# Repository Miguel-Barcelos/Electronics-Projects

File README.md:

# Controle motor elétrico PMSM
Este repositório contém projetos de eletrônica, incluindo circuitos eletrônicos, simulações e design de PCBs.

## Visão Geral do Projeto
O objetivo principal deste trabalho é 

## 📂 Estrutura do Repositório

*   `/data`: xxxxxxxxxxxxxxxxxxxxxxxxxxxxxxxxxxxxxxxxxxxxxxxxxxxxxxxxx
*   `/src`: xxxxxxxxxxxxxxxxxxxxxxxxxxxxxxxxxxxxxxxxxxxxxxxxxxxxxxxxx
*   `/project`: xxxxxxxxxxxxxxxxxxxxxxxxxxxxxxxxxxxxxxxxxxxxxxxxxxxxxxxxx
*   `/figures`: xxxxxxxxxxxxxxxxxxxxxxxxxxxxxxxxxxxxxxxxxxxxxxxxxxxxxxxxx

## 🎛️ Detalhes do Sistema Dinâmico

xxxxxxxxxxxxxxxxxxxxxxxxxxxxxxxxxxxxxxxxxxxxxxxxxxxxxxxxx

## 💻 Requisitos e Tecnologias

xxxxxxxxxxxxxxxxxxxxxxxxxxxxxxxxxxxxxxxxxxxxxxxxxxxxxxxxx

### Toolboxes Necessárias:
* xxxxxxxxxxxxxxxxxxxxxxxxxxxxxxxxxxxxxxxxxxxxxxxxxxxxxxxxx
* xxxxxxxxxxxxxxxxxxxxxxxxxxxxxxxxxxxxxxxxxxxxxxxxxxxxxxxxx

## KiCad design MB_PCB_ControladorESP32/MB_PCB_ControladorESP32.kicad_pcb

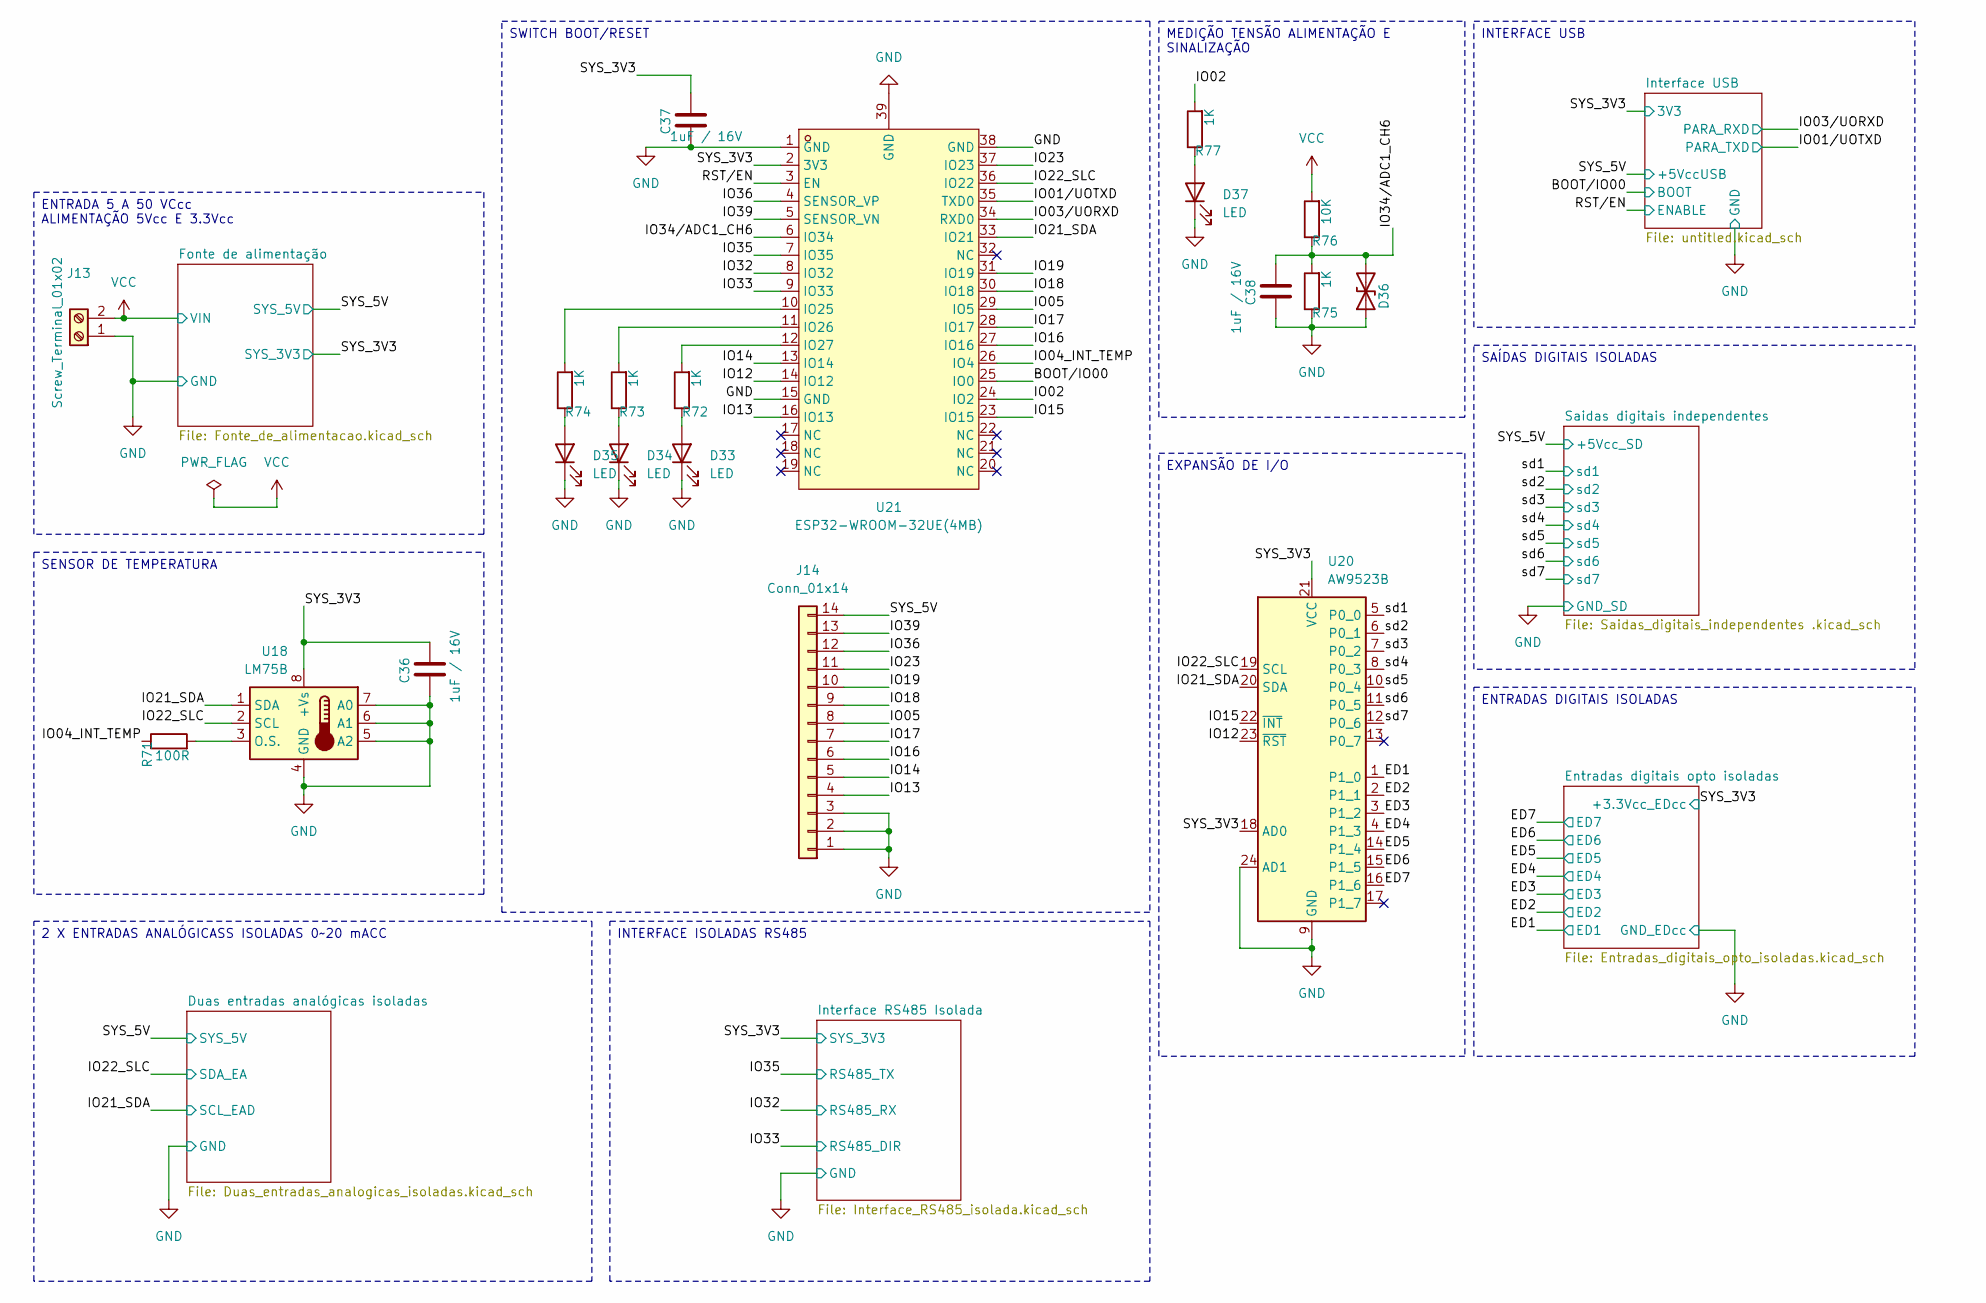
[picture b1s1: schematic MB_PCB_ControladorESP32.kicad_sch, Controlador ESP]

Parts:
C36, C37, C38: 1uF / 16V; C_Elec_4x5.4
D33, D34, D35, D37: LED; LED_0805_2012Metric_Pad1.15x1.40mm_HandSolder
D36: D_TVS; SOD-523_L1.2-W0.8-LS1.6-BI
J13: Screw_Terminal_01x02; TerminalBlock_TE_282834-2_1x02_P2.54mm_Horizontal
J14: Conn_01x14; PinHeader_1x14_P2.54mm_Vertical
R71: 100R; R_0805_2012Metric_Pad1.20x1.40mm_HandSolder
R72, R73, R74, R75, R77: 1K; R_0805_2012Metric_Pad1.20x1.40mm_HandSolder
R76: 10K; R_0805_2012Metric_Pad1.20x1.40mm_HandSolder
U18: LM75B; SOP-8_3.76x4.96mm_P1.27mm
U20: AW9523B; QFN-24-1EP_4x4mm_P0.5mm_EP2.7x2.7mm
U21: ESP32-WROOM-32UE(4MB); WIFI-SMD_ESP32-WROOM-32UE; LCSC Part C701344

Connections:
+3.3Vcc_EDcc: C36.2, C37.2, U18.8 (+Vs), U20.18 (AD0), U20.21 (VCC), U21.2 (3V3); also elsewhere on the board
+5VccUSB: J14.14; also elsewhere on the board
/BOOT/IO00: U21.25 (IO0); also elsewhere on the board
/ED1: U20.1 (P1_0); also elsewhere on the board
/ED2: U20.2 (P1_1); also elsewhere on the board
/ED3: U20.3 (P1_2); also elsewhere on the board
/ED4: U20.4 (P1_3); also elsewhere on the board
/ED5: U20.14 (P1_4); also elsewhere on the board
/ED6: U20.15 (P1_5); also elsewhere on the board
/ED7: U20.16 (P1_6); also elsewhere on the board
/IO01/UOTXD: U21.35 (TXD0); also elsewhere on the board
/IO02: R77.2, U21.24 (IO2)
/IO03/UORXD: U21.34 (RXD0); also elsewhere on the board
/IO04_INT_TEMP: R71.1, U21.26 (IO4)
/IO05: J14.8, U21.29 (IO5)
/IO12: U20.23 (~RST), U21.14 (IO12)
/IO13: J14.4, U21.16 (IO13)
/IO14: J14.5, U21.13 (IO14)
/IO15: U20.22 (~INT), U21.23 (IO15)
/IO16: J14.6, U21.27 (IO16)
/IO17: J14.7, U21.28 (IO17)
/IO18: J14.9, U21.30 (IO18)
/IO19: J14.10, U21.31 (IO19)
/IO21_SDA: U18.1 (SDA), U20.20 (SDA), U21.33 (IO21); also elsewhere on the board
/IO22_SLC: U18.2 (SCL), U20.19 (SCL), U21.36 (IO22); also elsewhere on the board
/IO23: J14.11, U21.37 (IO23)
/IO32: U21.8 (IO32); also elsewhere on the board
/IO33: U21.9 (IO33); also elsewhere on the board
/IO34/ADC1_CH6: C38.2, D36.2 (A2), R75.2, R76.1, U21.6 (IO34)
/IO35: U21.7 (IO35); also elsewhere on the board
/IO36: J14.12, U21.4 (SENSOR_VP)
/IO39: J14.13, U21.5 (SENSOR_VN)
/RST/EN: U21.3 (EN); also elsewhere on the board
/sd1: U20.5 (P0_0); also elsewhere on the board
/sd2: U20.6 (P0_1); also elsewhere on the board
/sd3: U20.7 (P0_2); also elsewhere on the board
/sd4: U20.8 (P0_3); also elsewhere on the board
/sd5: U20.10 (P0_4); also elsewhere on the board
/sd6: U20.11 (P0_5); also elsewhere on the board
/sd7: U20.12 (P0_6); also elsewhere on the board
GND: C36.1, C37.1, C38.1, D33.1 (K), D34.1 (K), D35.1 (K), D36.1 (A1), D37.1 (K), J13.1, J14.1, J14.2, J14.3, R75.1, U18.4 (GND), U18.5 (A2), U18.6 (A1), U18.7 (A0), U20.9 (GND), U20.24 (AD1), U20.25 (GND), U21.1 (GND), U21.15 (GND), U21.38 (GND), U21.39 (GND); also elsewhere on the board
unnamed: D33.2 (A), R72.1
unnamed: D34.2 (A), R73.1
unnamed: D35.2 (A), R74.1
unnamed: D37.2 (A), R77.1
unnamed: R71.2, U18.3 (O.S.)
unnamed: R74.2, U21.10 (IO25)
unnamed: R73.2, U21.11 (IO26)
unnamed: R72.2, U21.12 (IO27)
VCC: J13.2, R76.2; also elsewhere on the board

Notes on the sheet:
INTERFACE ISOLADAS RS485
2 X ENTRADAS ANALÓGICASS ISOLADAS 0~20 mACC
SWITCH BOOT/RESET
SAÍDAS DIGITAIS ISOLADAS
ENTRADAS DIGITAIS ISOLADAS
EXPANSÃO DE I/O
ENTRADA 5 A 50 VCcc ALIMENTAÇÃO 5Vcc E 3.3Vcc
SENSOR DE TEMPERATURA
MEDIÇÃO TENSÃO ALIMENTAÇÃO E SINALIZAÇÃO
INTERFACE USB

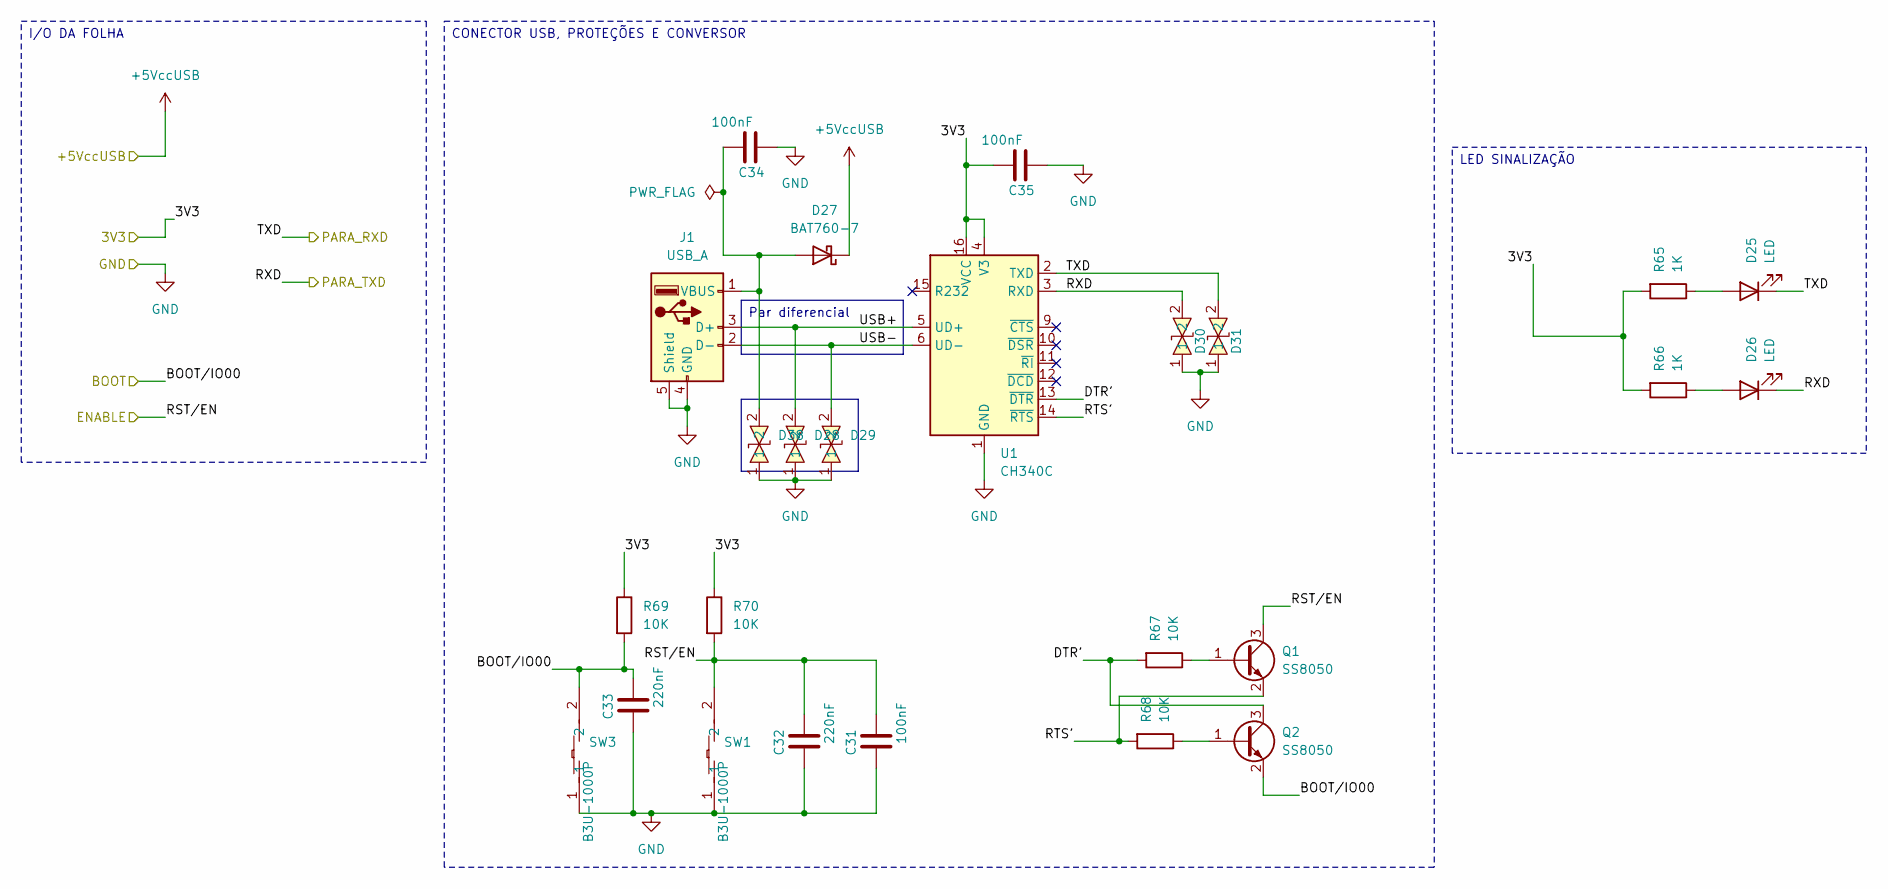
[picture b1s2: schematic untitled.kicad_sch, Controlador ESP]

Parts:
C31, C34, C35: 100nF; C_Elec_8x5.4
C32, C33: 220nF; C_Elec_8x5.4
D25, D26: LED; LED_0805_2012Metric_Pad1.15x1.40mm_HandSolder
D27: BAT760-7; SOD-523_L1.2-W0.8-LS1.6-BI
D28, D29, D30, D31, D38: LESD5D5.0CT1G; SOD-523_L1.2-W0.8-LS1.6-BI; LCSC Part C383211
J1: USB_A; USB_A_Molex_67643_Horizontal
Q1, Q2: SS8050; SOT-23
R65, R66: 1K; R_0805_2012Metric_Pad1.20x1.40mm_HandSolder
R67, R68, R69, R70: 10K; R_0805_2012Metric_Pad1.20x1.40mm_HandSolder
SW1, SW3: B3U-1000P; KEY-SMD_B3U-1000PM; LCSC Part C231329
U1: CH340C; SOIC-16_3.9x9.9mm_P1.27mm

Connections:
+3.3Vcc_EDcc: C35.2, R65.2, R66.2, R69.1, R70.1, U1.4 (V3), U1.16 (VCC); also elsewhere on the board
+5VccUSB: D27.1 (K); also elsewhere on the board
/BOOT/IO00: C33.2, Q2.2 (E), R69.2, SW3.2; also elsewhere on the board
/IO01/UOTXD: D26.1 (K), D30.2, U1.3 (RXD); also elsewhere on the board
/IO03/UORXD: D25.1 (K), D31.2, U1.2 (TXD); also elsewhere on the board
/Interface USB/DTR': Q2.3 (C), R67.2, U1.13 (~DTR)
/Interface USB/RTS': Q1.2 (E), R68.2, U1.14 (~RTS)
/Interface USB/USB+: D28.2, J1.3 (D+), U1.5 (UD+)
/Interface USB/USB-: D29.2, J1.2 (D-), U1.6 (UD-)
/RST/EN: C31.2, C32.2, Q1.3 (C), R70.2, SW1.2; also elsewhere on the board
GND: C31.1, C32.1, C33.1, C34.1, C35.1, D28.1, D29.1, D30.1, D31.1, D38.1, J1.4 (GND), J1.5 (Shield), SW1.1, SW3.1, U1.1 (GND); also elsewhere on the board
unnamed: D25.2 (A), R65.1
unnamed: D26.2 (A), R66.1
unnamed: C34.2, D27.2 (A), D38.2, J1.1 (VBUS)
unnamed: Q1.1 (B), R67.1
unnamed: Q2.1 (B), R68.1

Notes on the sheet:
I/O DA FOLHA
LED SINALIZAÇÃO
CONECTOR USB, PROTEÇÕES E CONVERSOR
Par diferencial

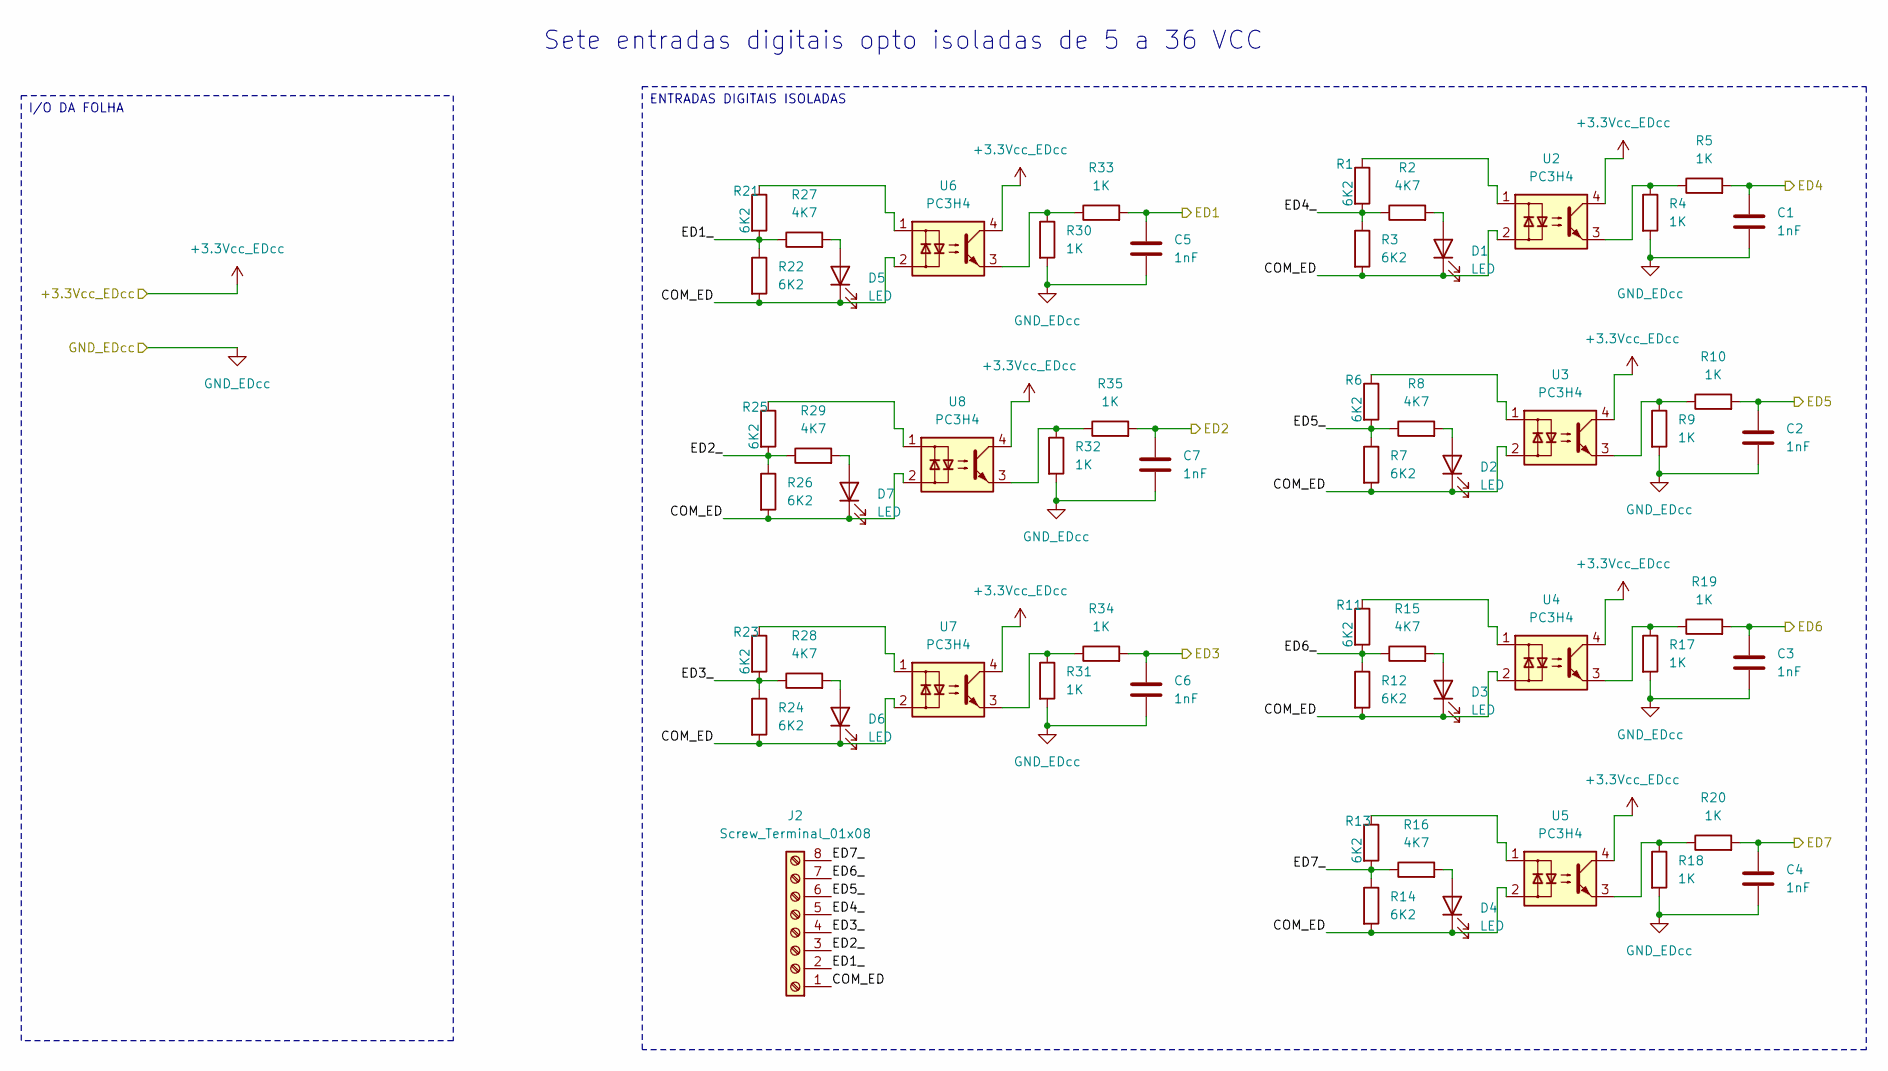
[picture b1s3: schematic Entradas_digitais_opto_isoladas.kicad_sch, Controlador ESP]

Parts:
C1, C2, C3, C4, C5, C6, C7: 1nF; C_1206_3216Metric_Pad1.33x1.80mm_HandSolder
D1, D2, D3, D4, D5, D6, D7: LED; LED_0805_2012Metric_Pad1.15x1.40mm_HandSolder
J2: Screw_Terminal_01x08; TerminalBlock_TE_282834-8_1x08_P2.54mm_Horizontal
R1, R3, R6, R7, R11, R12, R13, R14, R21, R22, R23, R24, R25, R26: 6K2; R_0805_2012Metric_Pad1.20x1.40mm_HandSolder
R2, R8, R15, R16, R27, R28, R29: 4K7; R_0805_2012Metric_Pad1.20x1.40mm_HandSolder
R4, R5, R9, R10, R17, R18, R19, R20, R30, R31, R32, R33, R34, R35: 1K; R_0805_2012Metric_Pad1.20x1.40mm_HandSolder
U2, U3, U4, U5, U6, U7, U8: PC3H4; SMDIP-4_W7.62mm

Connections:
+3.3Vcc_EDcc: U2.4, U3.4, U4.4, U5.4, U6.4, U7.4, U8.4; also elsewhere on the board
/ED1: C5.1, R33.2; also elsewhere on the board
/ED2: C7.1, R35.2; also elsewhere on the board
/ED3: C6.1, R34.2; also elsewhere on the board
/ED4: C1.1, R5.2; also elsewhere on the board
/ED5: C2.1, R10.2; also elsewhere on the board
/ED6: C3.1, R19.2; also elsewhere on the board
/ED7: C4.1, R20.2; also elsewhere on the board
/Entradas digitais opto isoladas/COM_ED: D1.1 (K), D2.1 (K), D3.1 (K), D4.1 (K), D5.1 (K), D6.1 (K), D7.1 (K), J2.1, R3.2, R7.2, R12.2, R14.2, R22.2, R24.2, R26.2, U2.2, U3.2, U4.2, U5.2, U6.2, U7.2, U8.2
/Entradas digitais opto isoladas/ED1_: J2.2, R21.2, R22.1, R27.1
/Entradas digitais opto isoladas/ED2_: J2.3, R25.2, R26.1, R29.1
/Entradas digitais opto isoladas/ED3_: J2.4, R23.2, R24.1, R28.1
/Entradas digitais opto isoladas/ED4_: J2.5, R1.2, R2.1, R3.1
/Entradas digitais opto isoladas/ED5_: J2.6, R6.2, R7.1, R8.1
/Entradas digitais opto isoladas/ED6_: J2.7, R11.2, R12.1, R15.1
/Entradas digitais opto isoladas/ED7_: J2.8, R13.2, R14.1, R16.1
GND: C1.2, C2.2, C3.2, C4.2, C5.2, C6.2, C7.2, R4.2, R9.2, R17.2, R18.2, R30.2, R31.2, R32.2; also elsewhere on the board
unnamed: D1.2 (A), R2.2
unnamed: D2.2 (A), R8.2
unnamed: D3.2 (A), R15.2
unnamed: D4.2 (A), R16.2
unnamed: D5.2 (A), R27.2
unnamed: D6.2 (A), R28.2
unnamed: D7.2 (A), R29.2
unnamed: R1.1, U2.1
unnamed: R4.1, R5.1, U2.3
unnamed: R6.1, U3.1
unnamed: R9.1, R10.1, U3.3
unnamed: R11.1, U4.1
unnamed: R13.1, U5.1
unnamed: R17.1, R19.1, U4.3
unnamed: R18.1, R20.1, U5.3
unnamed: R21.1, U6.1
unnamed: R23.1, U7.1
unnamed: R25.1, U8.1
unnamed: R30.1, R33.1, U6.3
unnamed: R31.1, R34.1, U7.3
unnamed: R32.1, R35.1, U8.3

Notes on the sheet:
Sete entradas digitais opto isoladas de 5 a 36 VCC
I/O DA FOLHA
ENTRADAS DIGITAIS ISOLADAS

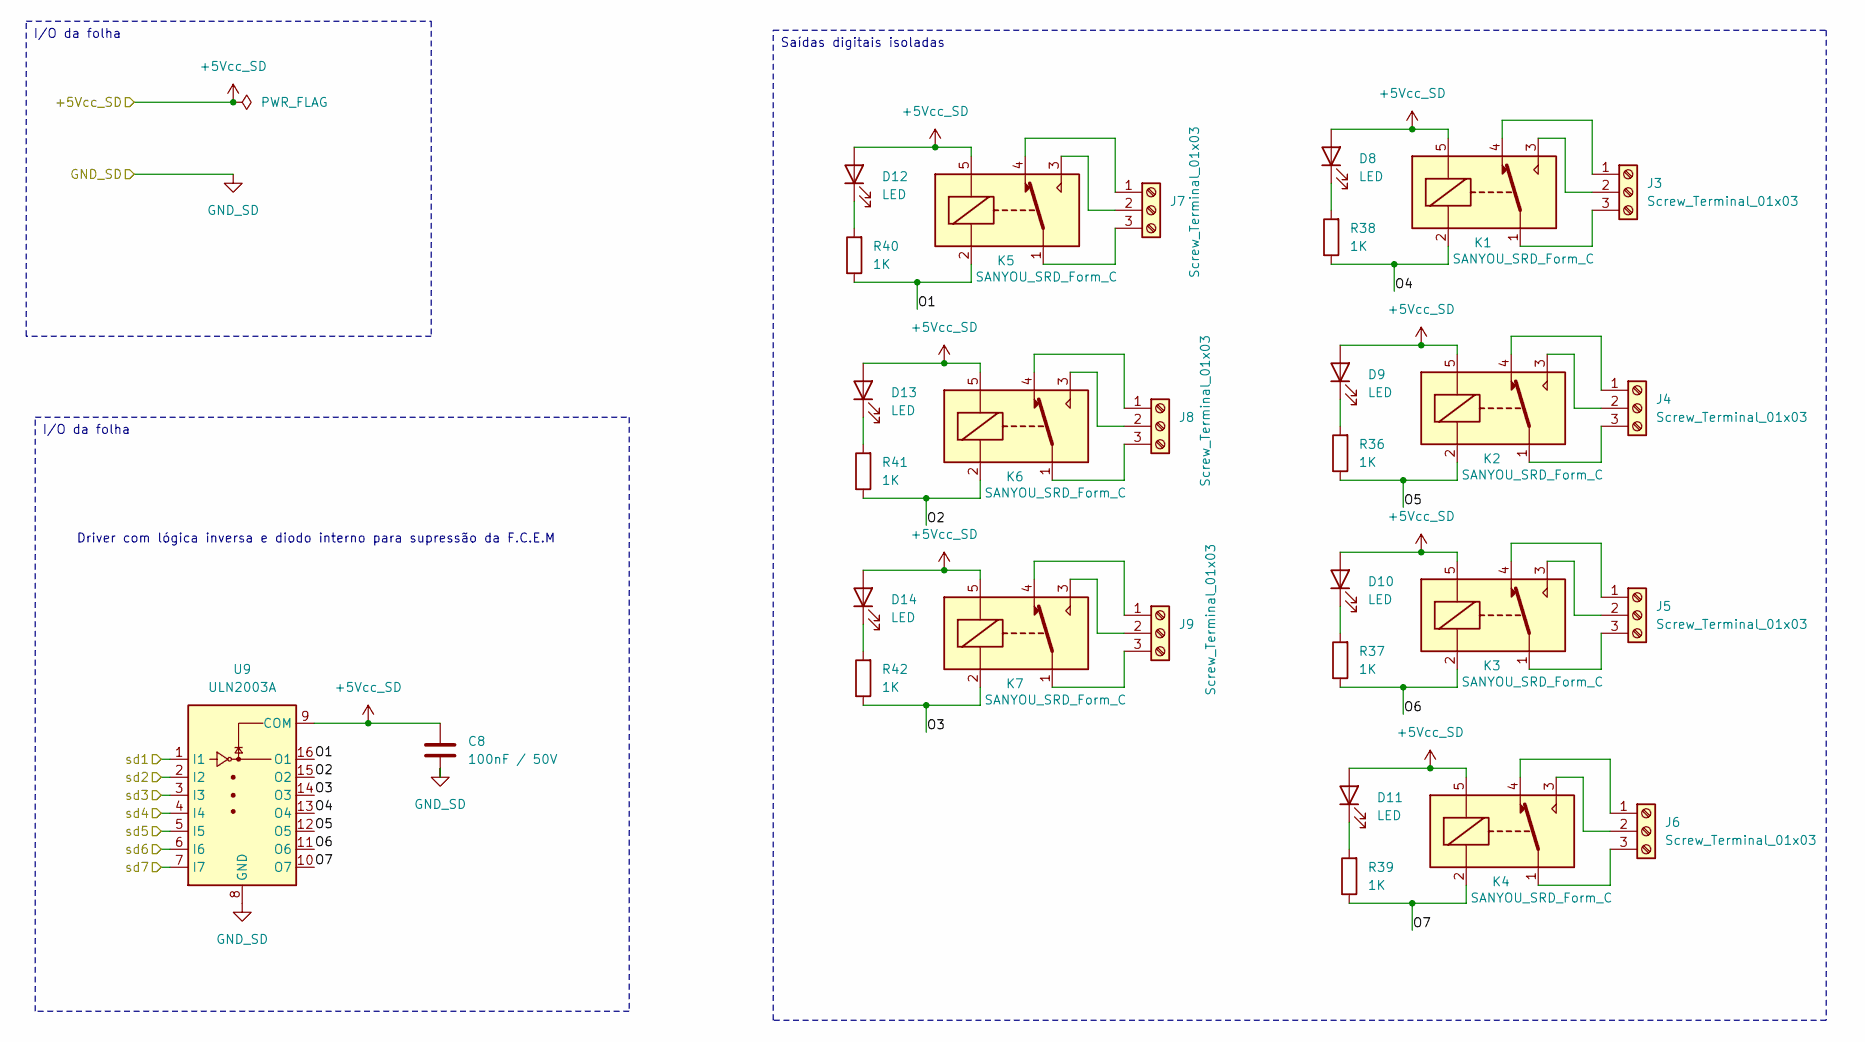
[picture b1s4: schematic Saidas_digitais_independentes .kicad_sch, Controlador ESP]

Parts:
C8: 100nF / 50V; C_1206_3216Metric_Pad1.33x1.80mm_HandSolder
D8, D9, D10, D11, D12, D13, D14: LED; LED_0805_2012Metric_Pad1.15x1.40mm_HandSolder
J3, J4, J5, J6, J7, J8, J9: Screw_Terminal_01x03; TerminalBlock_TE_282834-3_1x03_P2.54mm_Horizontal
K1, K2, K3, K4, K5, K6, K7: SANYOU_SRD_Form_C; Relay_SPDT_SANYOU_SRD_Series_Form_C
R36, R37, R38, R39, R40, R41, R42: 1K; R_0805_2012Metric_Pad1.20x1.40mm_HandSolder
U9: ULN2003A; DIP-16_W7.62mm

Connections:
+5VccUSB: C8.1, D8.2 (A), D9.2 (A), D10.2 (A), D11.2 (A), D12.2 (A), D13.2 (A), D14.2 (A), K1.5, K2.5, K3.5, K4.5, K5.5, K6.5, K7.5, U9.9 (COM); also elsewhere on the board
/Saidas digitais independentes/O1: K5.2, R40.1, U9.16 (O1)
/Saidas digitais independentes/O2: K6.2, R41.1, U9.15 (O2)
/Saidas digitais independentes/O3: K7.2, R42.1, U9.14 (O3)
/Saidas digitais independentes/O4: K1.2, R38.1, U9.13 (O4)
/Saidas digitais independentes/O5: K2.2, R36.1, U9.12 (O5)
/Saidas digitais independentes/O6: K3.2, R37.1, U9.11 (O6)
/Saidas digitais independentes/O7: K4.2, R39.1, U9.10 (O7)
/sd1: U9.1 (I1); also elsewhere on the board
/sd2: U9.2 (I2); also elsewhere on the board
/sd3: U9.3 (I3); also elsewhere on the board
/sd4: U9.4 (I4); also elsewhere on the board
/sd5: U9.5 (I5); also elsewhere on the board
/sd6: U9.6 (I6); also elsewhere on the board
/sd7: U9.7 (I7); also elsewhere on the board
GND: C8.2, U9.8 (GND); also elsewhere on the board
unnamed: D8.1 (K), R38.2
unnamed: D9.1 (K), R36.2
unnamed: D10.1 (K), R37.2
unnamed: D11.1 (K), R39.2
unnamed: D12.1 (K), R40.2
unnamed: D13.1 (K), R41.2
unnamed: D14.1 (K), R42.2
unnamed: J3.1, K1.4
unnamed: J3.2, K1.3
unnamed: J3.3, K1.1
unnamed: J4.1, K2.4
unnamed: J4.2, K2.3
unnamed: J4.3, K2.1
unnamed: J5.1, K3.4
unnamed: J5.2, K3.3
unnamed: J5.3, K3.1
unnamed: J6.1, K4.4
unnamed: J6.2, K4.3
unnamed: J6.3, K4.1
unnamed: J7.1, K5.4
unnamed: J7.2, K5.3
unnamed: J7.3, K5.1
unnamed: J8.1, K6.4
unnamed: J8.2, K6.3
unnamed: J8.3, K6.1
unnamed: J9.1, K7.4
unnamed: J9.2, K7.3
unnamed: J9.3, K7.1

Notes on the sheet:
Driver com lógica inversa e diodo interno para supressão da F.C.E.M
Saídas digitais isoladas
I/O da folha
I/O da folha

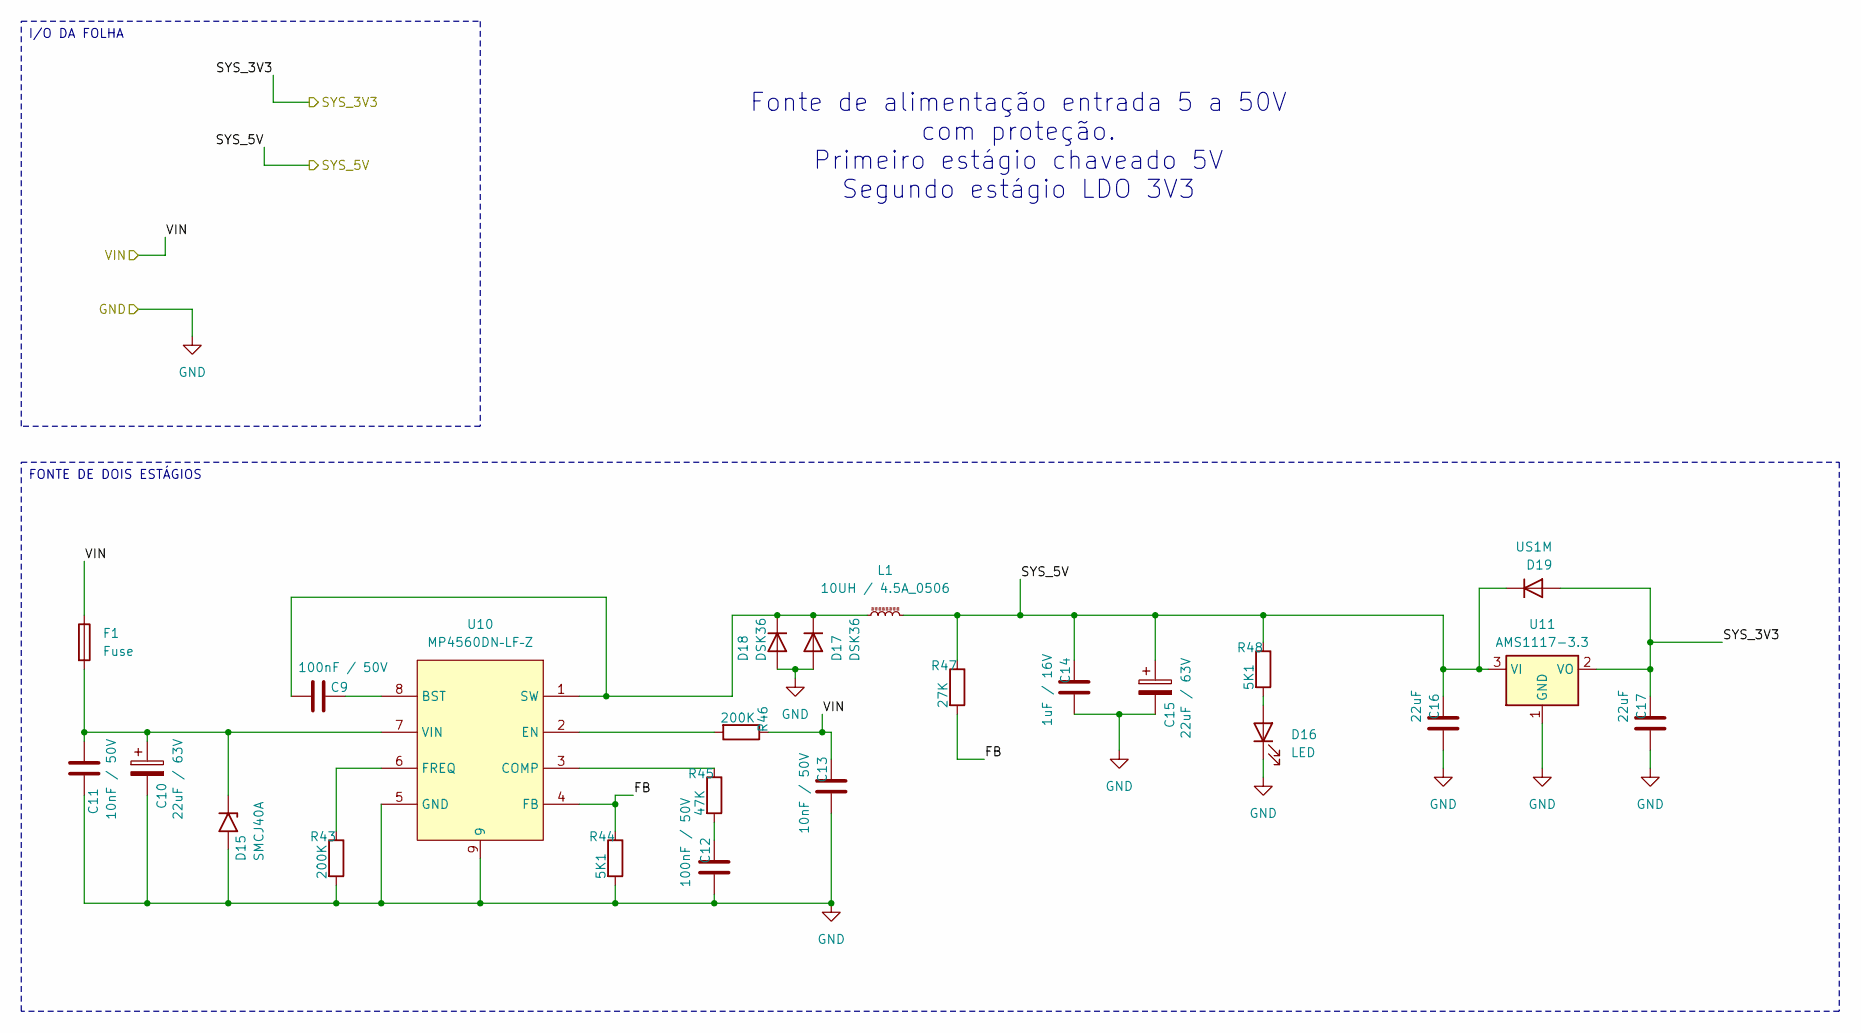
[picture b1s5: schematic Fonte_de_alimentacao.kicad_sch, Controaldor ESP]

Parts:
C9, C12: 100nF / 50V; C_0805_2012Metric_Pad1.18x1.45mm_HandSolder
C10: 22uF / 63V; CP_Elec_6.3x5.9
C11: 10nF / 50V; C_0805_2012Metric_Pad1.18x1.45mm_HandSolder
C13: 10nF / 50V; CP_Elec_10x12.5
C14: 1uF / 16V; C_Elec_3x5.4
C15: 22uF / 63V; CP_Elec_10x12.5
C16, C17: 22uF; C_Elec_8x5.4
D15: SMCJ40A; D_SMC
D16: LED; LED_0805_2012Metric_Pad1.15x1.40mm_HandSolder
D17, D18: DSK36; D_SOD-523
D19: US1M; D_SMA
F1: Fuse; Fuse_Bourns_MF-RG300
L1: 10UH / 4.5A_0506; L_Cenker_CKCS6020
R43, R46: 200K; R_0805_2012Metric_Pad1.20x1.40mm_HandSolder
R44, R48: 5K1; R_0805_2012Metric_Pad1.20x1.40mm_HandSolder
R45: 47K; R_0805_2012Metric_Pad1.20x1.40mm_HandSolder
R47: 27K; R_0805_2012Metric_Pad1.20x1.40mm_HandSolder
U10: MP4560DN–LF–Z; SOIC-8_L4.9-W3.9-P1.27-LS6.0-BL-EP3.1-1; LCSC Part C40133
U11: AMS1117-3.3; SOT-223-3_TabPin2

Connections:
+3.3Vcc_EDcc: C17.2, D19.2 (A), U11.2 (VO); also elsewhere on the board
+5VccUSB: C14.2, C15.1, C16.2, D19.1 (K), L1.2, R47.1, R48.1, U11.3 (VI); also elsewhere on the board
/Fonte de alimentação/FB: R44.1, R47.2, U10.4 (FB)
GND: C10.2, C11.1, C12.1, C13.1, C14.1, C15.2, C16.1, C17.1, D15.2 (A2), D16.1 (K), D17.2 (A), D18.2 (A), R43.2, R44.2, U10.5 (GND), U10.9, U11.1 (GND); also elsewhere on the board
unnamed: C12.2, R45.2
unnamed: C10.1, C11.2, D15.1 (A1), F1.2, U10.7 (VIN)
unnamed: D16.2 (A), R48.2
unnamed: C9.1, D17.1 (K), D18.1 (K), L1.1, U10.1 (SW)
unnamed: C9.2, U10.8 (BST)
unnamed: R45.1, U10.3 (COMP)
unnamed: R46.2, U10.2 (EN)
unnamed: R43.1, U10.6 (FREQ)
VCC: C13.2, F1.1, R46.1; also elsewhere on the board

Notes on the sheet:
Fonte de alimentação entrada 5 a 50V com proteção. Primeiro estágio chaveado 5V Segundo estágio LDO 3V3
FONTE DE DOIS ESTÁGIOS
I/O DA FOLHA

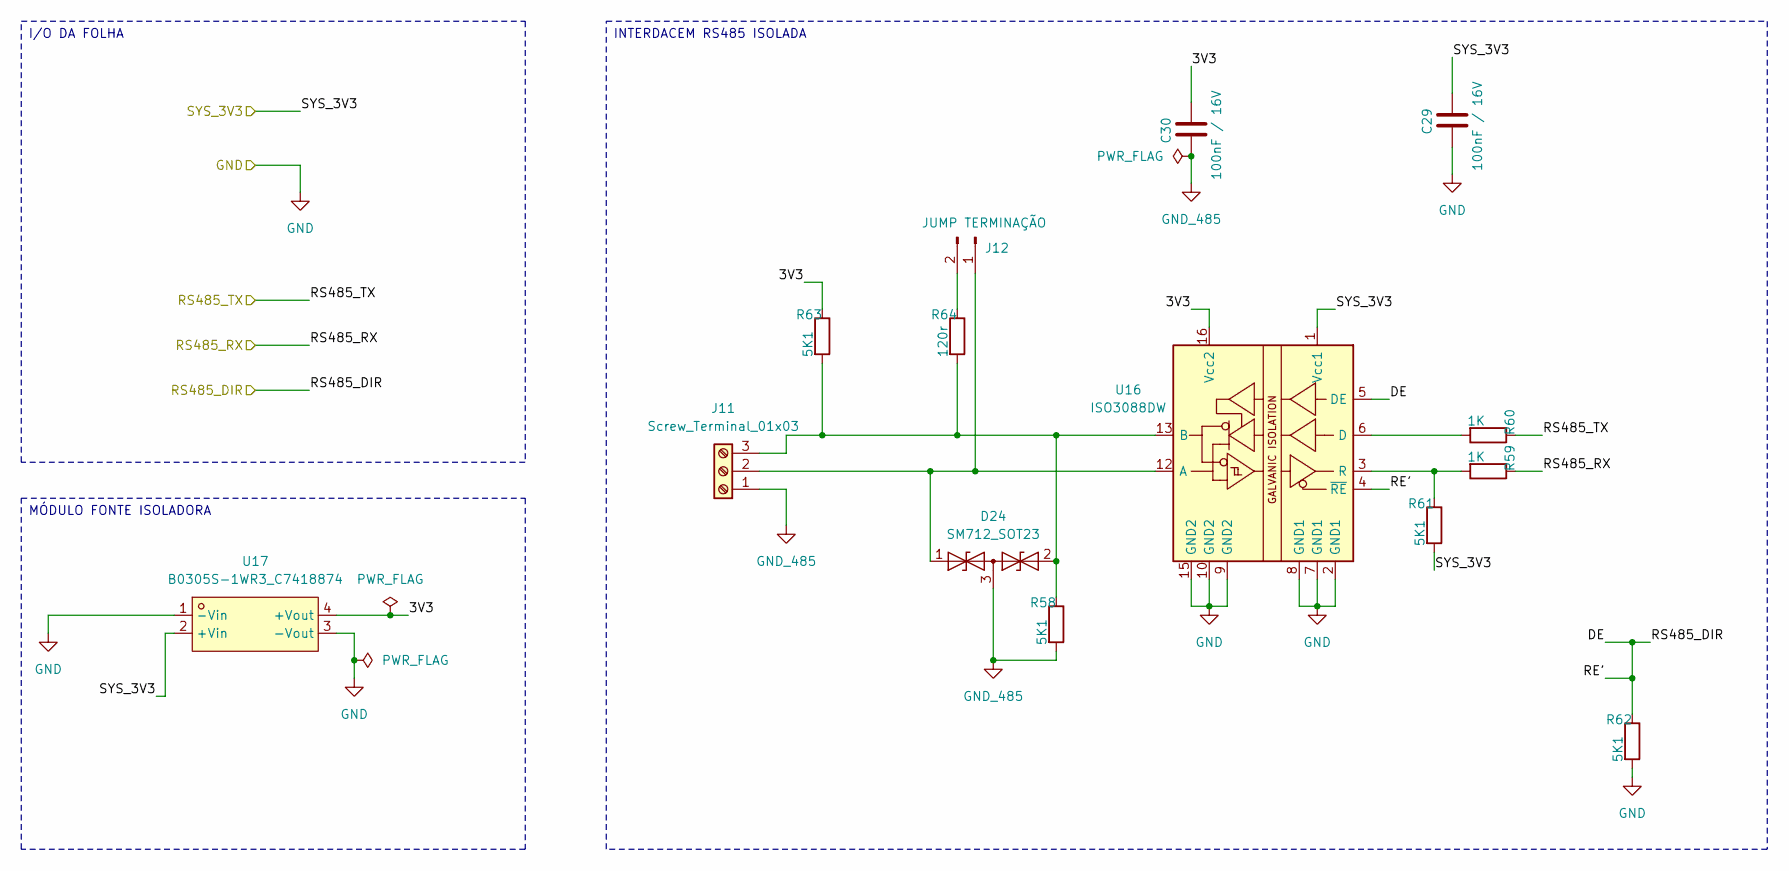
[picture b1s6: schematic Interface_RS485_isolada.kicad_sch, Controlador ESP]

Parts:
C29, C30: 100nF / 16V; C_Elec_6.3x5.8
D24: SM712_SOT23; SOT-23
J11: Screw_Terminal_01x03; TerminalBlock_TE_282834-3_1x03_P2.54mm_Horizontal
J12: JUMP TERMINAÇÃO; PinHeader_1x02_P2.54mm_Vertical
R58, R61, R62, R63: 5K1; R_0805_2012Metric_Pad1.20x1.40mm_HandSolder
R59, R60: 1K; R_0805_2012Metric_Pad1.20x1.40mm_HandSolder
R64: 120r; R_0805_2012Metric_Pad1.20x1.40mm_HandSolder
U16: ISO3088DW; SOIC-16W_7.5x10.3mm_P1.27mm
U17: B0305S-1WR3_C7418874; PWRM-TH_YLPTEC_BXXXXS-1WR3; LCSC Part C7418874

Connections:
+3.3Vcc_EDcc: C29.2, R61.2, U16.1 (Vcc1), U17.2 (+Vin); also elsewhere on the board
/IO32: R59.1; also elsewhere on the board
/IO33: R62.1, U16.4 (~RE), U16.5 (DE); also elsewhere on the board
/IO35: R60.1; also elsewhere on the board
/Interface RS485 Isolada/3V3: C30.2, R63.1, U16.16 (Vcc2), U17.4 (+Vout)
GND: C29.1, R62.2, U16.2 (GND1), U16.7 (GND1), U16.8 (GND1), U16.9 (GND2), U16.10 (GND2), U16.15 (GND2), U17.1 (-Vin), U17.3 (-Vout); also elsewhere on the board
GND_485: C30.1, D24.3 (common), J11.1, R58.2
unnamed: D24.1 (A1), J11.2, J12.1, U16.12 (A)
unnamed: D24.2 (A2), J11.3, R58.1, R63.2, R64.2, U16.13 (B)
unnamed: J12.2, R64.1
unnamed: R60.2, U16.6 (D)
unnamed: R59.2, R61.1, U16.3 (R)

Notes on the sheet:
MÓDULO FONTE ISOLADORA
I/O DA FOLHA
INTERDACEM RS485 ISOLADA

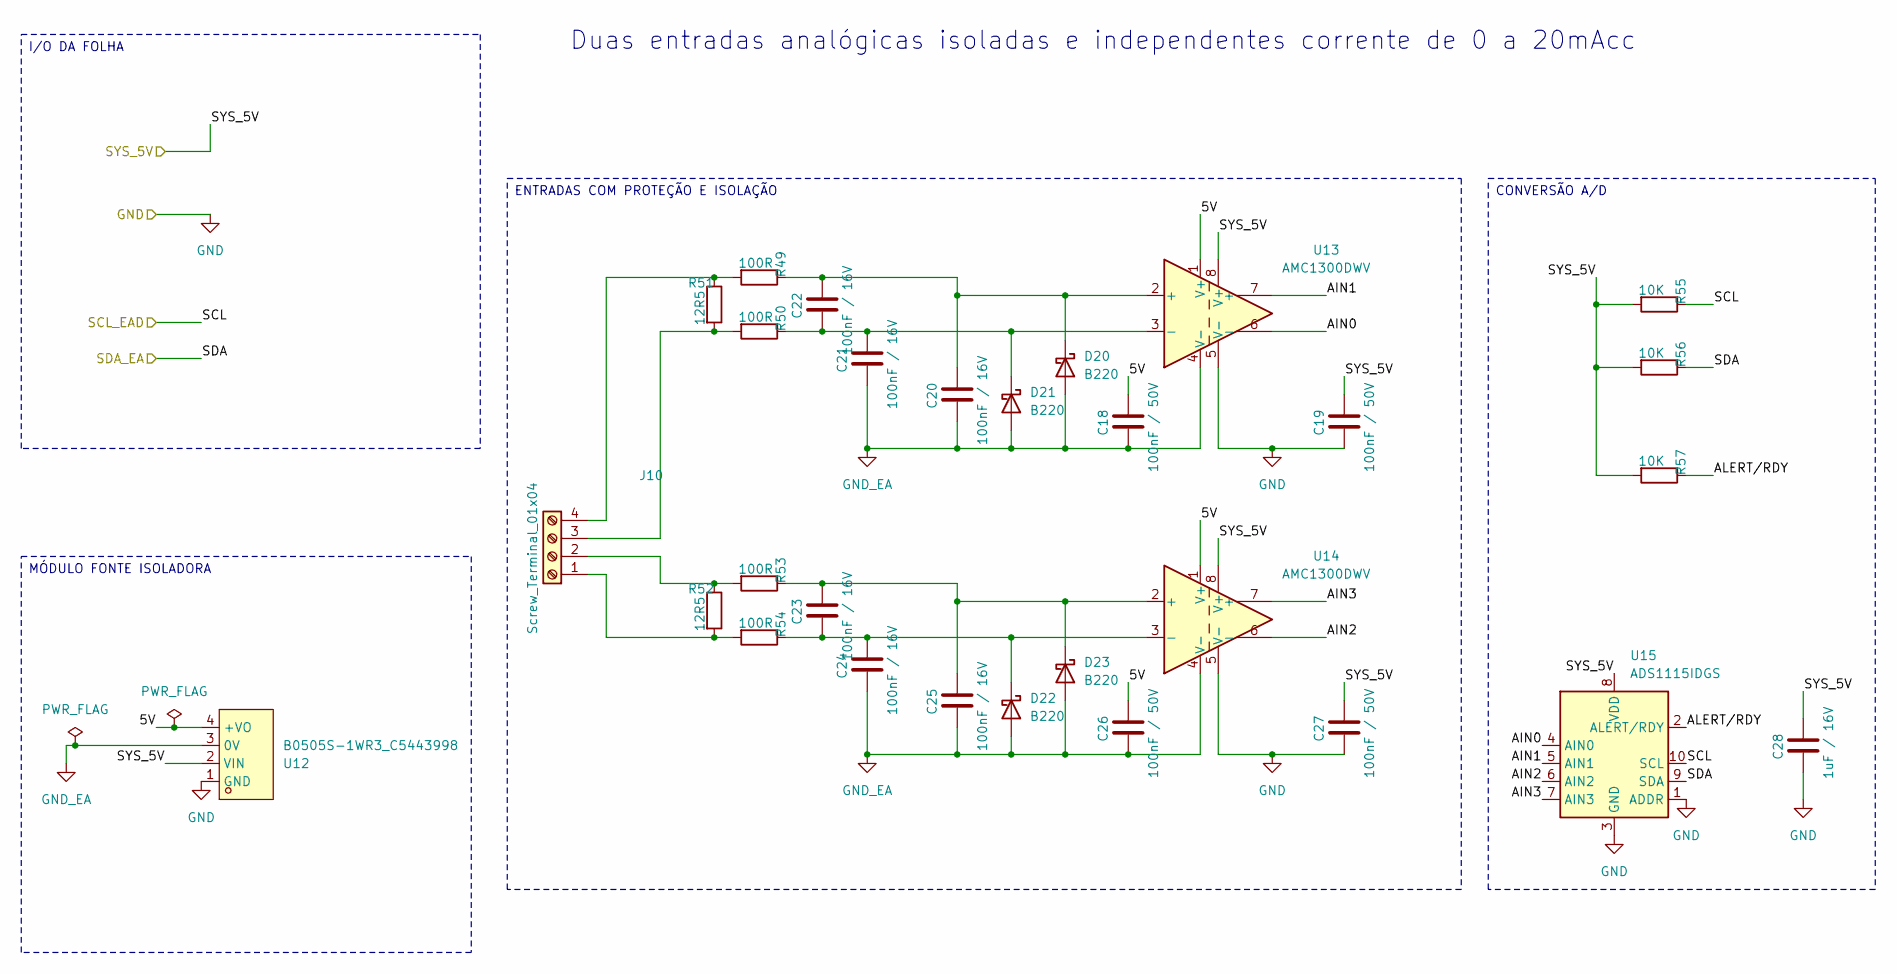
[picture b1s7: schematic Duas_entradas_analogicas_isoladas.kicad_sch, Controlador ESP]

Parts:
C18, C19, C26, C27: 100nF / 50V; C_0805_2012Metric_Pad1.18x1.45mm_HandSolder
C20, C21, C22, C23, C24, C25: 100nF / 16V; C_0805_2012Metric_Pad1.18x1.45mm_HandSolder
C28: 1uF / 16V; C_0805_2012Metric_Pad1.18x1.45mm_HandSolder
D20, D21, D22, D23: B220; D_SMB
J10: Screw_Terminal_01x04; TerminalBlock_TE_282834-4_1x04_P2.54mm_Horizontal
R49, R50, R53, R54: 100R; R_0805_2012Metric_Pad1.20x1.40mm_HandSolder
R51, R52: 12R5; R_0805_2012Metric_Pad1.20x1.40mm_HandSolder
R55, R56, R57: 10K; R_0805_2012Metric_Pad1.20x1.40mm_HandSolder
U12: B0505S-1WR3_C5443998; PWRM-TH_B0505S-1WR3T; LCSC Part C5443998
U13, U14: AMC1300DWV; SOIC-8_7.5x5.85mm_P1.27mm
U15: ADS1115IDGS; TSSOP-10_3x3mm_P0.5mm

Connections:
+5VccUSB: C19.2, C27.2, C28.2, R55.2, R56.2, R57.2, U12.2 (VIN), U13.8 (V+), U14.8 (V+), U15.8 (VDD); also elsewhere on the board
/Duas entradas analógicas isoladas/5V: C18.2, C26.2, U12.4 (+VO), U13.1 (V+), U14.1 (V+)
/Duas entradas analógicas isoladas/AIN0: U13.6 (-), U15.4 (AIN0)
/Duas entradas analógicas isoladas/AIN1: U13.7 (+), U15.5 (AIN1)
/Duas entradas analógicas isoladas/AIN2: U14.6 (-), U15.6 (AIN2)
/Duas entradas analógicas isoladas/AIN3: U14.7 (+), U15.7 (AIN3)
/Duas entradas analógicas isoladas/ALERT/RDY: R57.1, U15.2 (ALERT/RDY)
/IO21_SDA: R55.1, U15.10 (SCL); also elsewhere on the board
/IO22_SLC: R56.1, U15.9 (SDA); also elsewhere on the board
GND: C19.1, C27.1, C28.1, U12.1 (GND), U13.5 (V-), U14.5 (V-), U15.1 (ADDR), U15.3 (GND); also elsewhere on the board
GND_EA: C18.1, C20.1, C21.1, C24.1, C25.1, C26.1, D20.2 (A), D21.2 (A), D22.2 (A), D23.2 (A), U12.3 (0V), U13.4 (V-), U14.4 (V-)
unnamed: C20.2, C22.2, D20.1 (K), R49.1, U13.2 (+)
unnamed: C21.2, C22.1, D21.1 (K), R50.1, U13.3 (-)
unnamed: C23.1, C24.2, D22.1 (K), R54.1, U14.3 (-)
unnamed: C23.2, C25.2, D23.1 (K), R53.1, U14.2 (+)
unnamed: J10.1, R52.2, R54.2
unnamed: J10.2, R52.1, R53.2
unnamed: J10.3, R50.2, R51.2
unnamed: J10.4, R49.2, R51.1

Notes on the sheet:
Duas entradas analógicas isoladas e independentes corrente de 0 a 20mAcc
I/O DA FOLHA
CONVERSÃO A/D
MÓDULO FONTE ISOLADORA
ENTRADAS COM PROTEÇÃO E ISOLAÇÃO
